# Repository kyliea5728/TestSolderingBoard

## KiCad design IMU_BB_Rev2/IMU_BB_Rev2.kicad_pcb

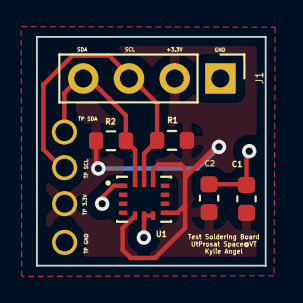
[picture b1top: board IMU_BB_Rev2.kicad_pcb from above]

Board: 2 copper layers, 12.7 x 12.7 mm, 10 parts (0 on the bottom side), 4 nets.

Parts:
C1, C2: 100nF; C_0603_1608Metric
J1: Conn_01x04; PinHeader_1x04_P2.54mm_Vertical
R1, R2: 10K; R_0603_1608Metric
TP1: 3.3V Test Point; TestPoint_1.0mm
TP2: GND Test Point; TestPoint_1.0mm
TP3: CLK Test Point; TestPoint_1.0mm
TP4: Data Line Test Point; TestPoint_1.0mm
U1: BMI270; XDCR_BMI270

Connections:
+3V3: C1.2, C2.2, J1.2, R1.2, R2.2, TP1.1, U1.5 (VDDIO), U1.8 (VDD), U1.12 (CSB)
/IMU_A_SCL: J1.3, R1.1, TP3.1, U1.13 (SCX)
/IMU_A_SDA: J1.4, R2.1, TP4.1, U1.14 (SDX)
GND: C1.1, C2.1, J1.1, TP2.1, U1.1 (SDO), U1.6 (GNDIO), U1.7 (GND)

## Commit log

2022-06-24 redid PCB
2022-08-24 getting started
